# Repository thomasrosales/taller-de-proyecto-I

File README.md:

# Taller de Proyecto I

Ingeniería en Computación - Materia Taller de Proyecto I

## Introducción

Por parte de la cátedra se propuso realizar un vúmetro digital de 8 bandas utilizando la placa de desarrollo EDU-CIAA, un teclado para comunicaicón con el usuario y una matriz de led para la posterior visulización para cumplir con la funcionalidad de un vúmetro.

## Autores

* **Alexandroff, Maximiliano** - *Desarrollo de software y Testeo de PCB* 
* **Gauna, Julián** - *Soldadura de componentes y armado de la PCB*
* **Fernandes Da Ponte, Emir** - *Diseño de PCB* 
* **Rosales, Tomás** - *Desarrollo de software y Testeo de PCB*

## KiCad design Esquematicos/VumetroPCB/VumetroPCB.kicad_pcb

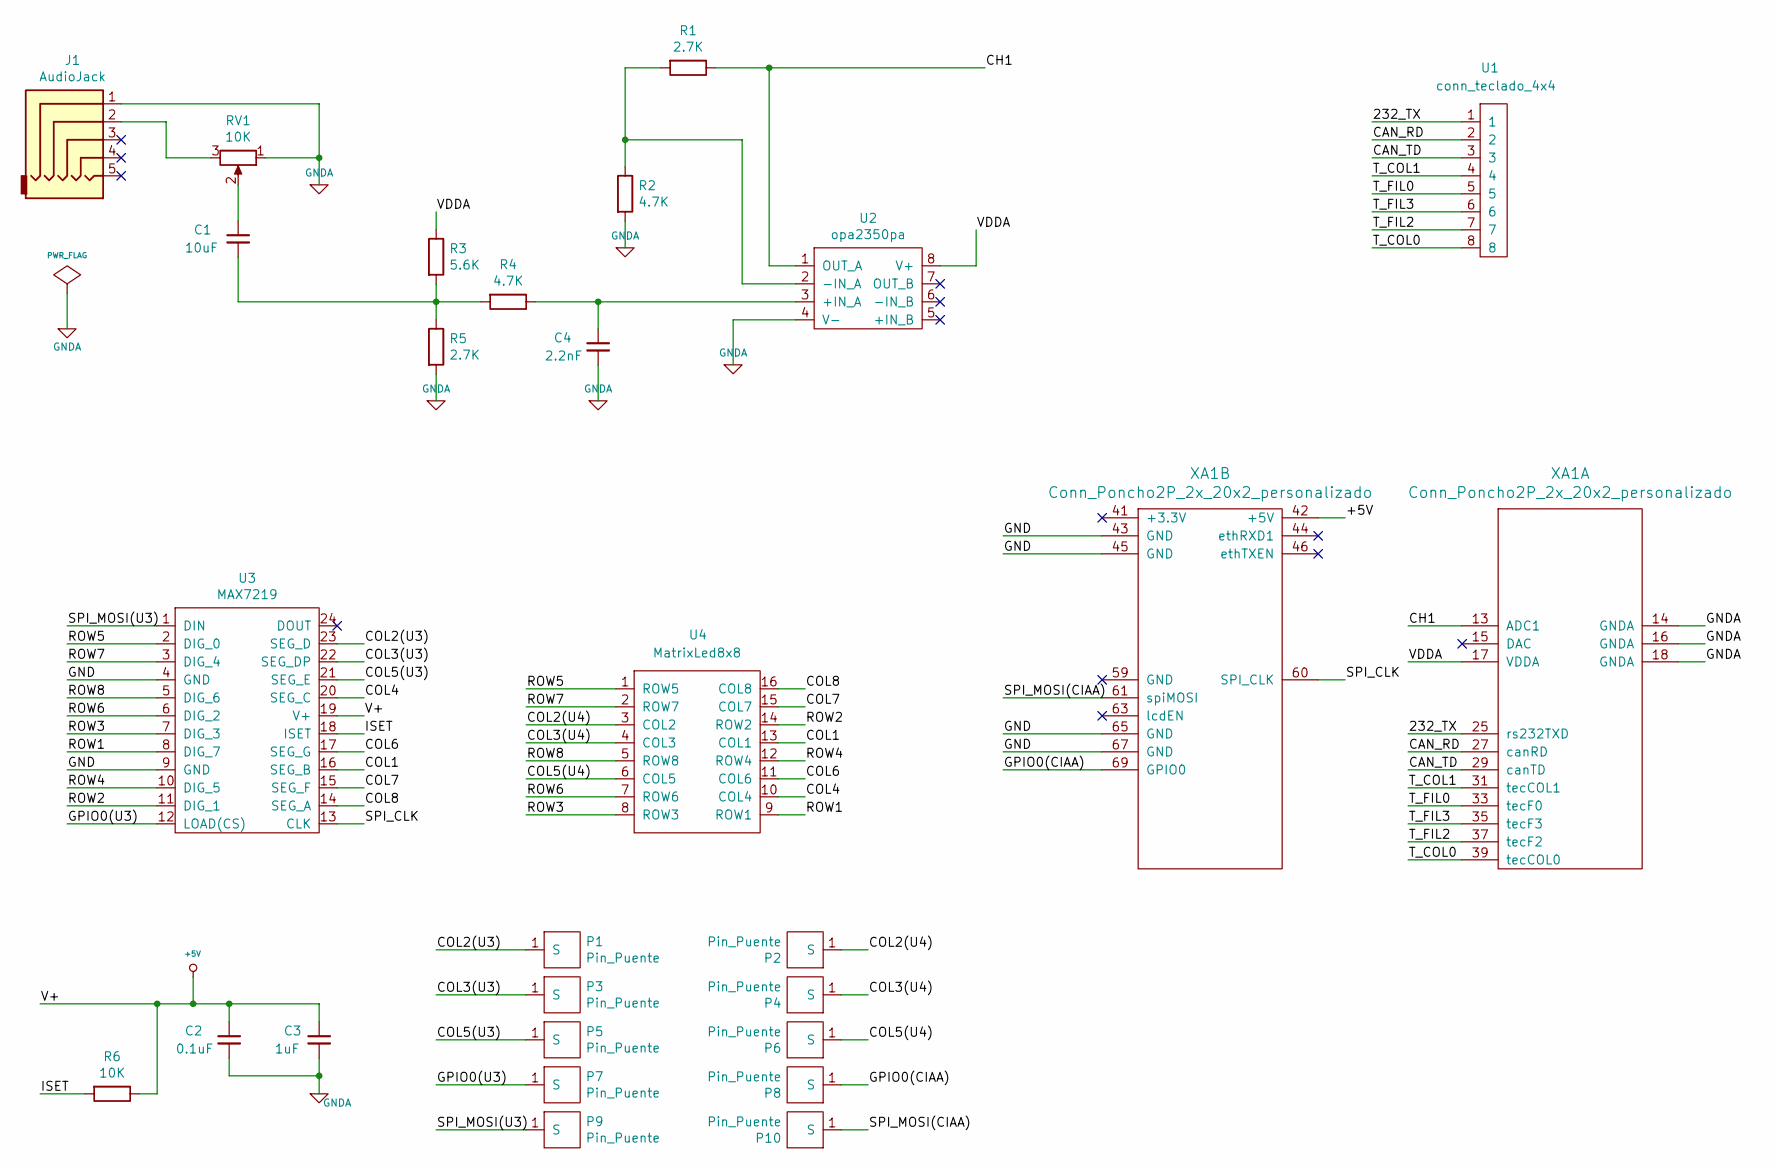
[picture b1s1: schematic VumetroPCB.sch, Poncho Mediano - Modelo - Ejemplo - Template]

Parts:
C1: 10uF; Capacitor
C2: 0.1uF; Capacitor_Disco
C3: 1uF; Capacitor
C4: 2.2nF; Capacitor_Disco
J1: AudioJack
P1, P2, P3, P4, P5, P6, P7, P8, P9, P10: Pin_Puente
R1, R5: 2.7K; Resistor
R2, R4: 4.7K; Resistor
R3: 5.6K; Resistor
R6: 10K; Resistor
RV1: 10K; Potentiometer_Bourns
U1: conn_teclado_4x4; conn_teclado4x4
U2: opa2350pa; OPA2350PA
U3: MAX7219
U4: MatrixLed8x8; Matriz_8x8
XA1: Conn_Poncho2P_2x_20x2_personalizado; Conn_Poncho_Personalizado

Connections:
+5V: C2.1, C3.1, R6.1, U3.19 (V+), XA1.42 (+5V)
/232_TX: U1.1, XA1.25 (rs232TXD)
/CAN_RD: U1.2, XA1.27 (canRD)
/CAN_TD: U1.3, XA1.29 (canTD)
/CH1: R1.1, U2.1 (OUT_A), XA1.13 (ADC1)
/COL1: U3.16 (SEG_B), U4.13 (COL1)
/COL2(U3): P1.1, U3.23 (SEG_D)
/COL2(U4): P2.1, U4.3 (COL2)
/COL3(U3): P3.1, U3.22 (SEG_DP)
/COL3(U4): P4.1, U4.4 (COL3)
/COL4: U3.20 (SEG_C), U4.10 (COL4)
/COL5(U3): P5.1, U3.21 (SEG_E)
/COL5(U4): P6.1, U4.6 (COL5)
/COL6: U3.17 (SEG_G), U4.11 (COL6)
/COL7: U3.15 (SEG_F), U4.15 (COL7)
/COL8: U3.14 (SEG_A), U4.16 (COL8)
/GND: U3.4 (GND), U3.9 (GND), XA1.43 (GND), XA1.45 (GND), XA1.65 (GND), XA1.67 (GND)
/GPIO0(CIAA): P8.1, XA1.69 (GPIO0)
/GPIO0(U3): P7.1, U3.12 (LOAD(CS))
/ISET: R6.2, U3.18 (ISET)
/ROW1: U3.8 (DIG_7), U4.9 (ROW1)
/ROW2: U3.11 (DIG_1), U4.14 (ROW2)
/ROW3: U3.7 (DIG_3), U4.8 (ROW3)
/ROW4: U3.10 (DIG_5), U4.12 (ROW4)
/ROW5: U3.2 (DIG_0), U4.1 (ROW5)
/ROW6: U3.6 (DIG_2), U4.7 (ROW6)
/ROW7: U3.3 (DIG_4), U4.2 (ROW7)
/ROW8: U3.5 (DIG_6), U4.5 (ROW8)
/SPI_CLK: U3.13 (CLK), XA1.60 (SPI_CLK)
/SPI_MOSI(CIAA): P10.1, XA1.61 (spiMOSI)
/SPI_MOSI(U3): P9.1, U3.1 (DIN)
/T_COL0: U1.8, XA1.39 (tecCOL0)
/T_COL1: U1.4, XA1.31 (tecCOL1)
/T_FIL0: U1.5, XA1.33 (tecF0)
/T_FIL2: U1.7, XA1.37 (tecF2)
/T_FIL3: U1.6, XA1.35 (tecF3)
/VDDA: R3.1, U2.8 (V+), XA1.17 (VDDA)
GNDA: C2.2, C3.2, C4.2, J1.1, R2.2, R5.2, RV1.1, U2.4 (V-), XA1.14 (GNDA), XA1.16 (GNDA), XA1.18 (GNDA)
unnamed: C1.1, RV1.2
unnamed: C1.2, R3.2, R4.2, R5.1
unnamed: C4.1, R4.1, U2.3 (+IN_A)
unnamed: J1.2, RV1.3
unnamed: R1.2, R2.1, U2.2 (-IN_A)

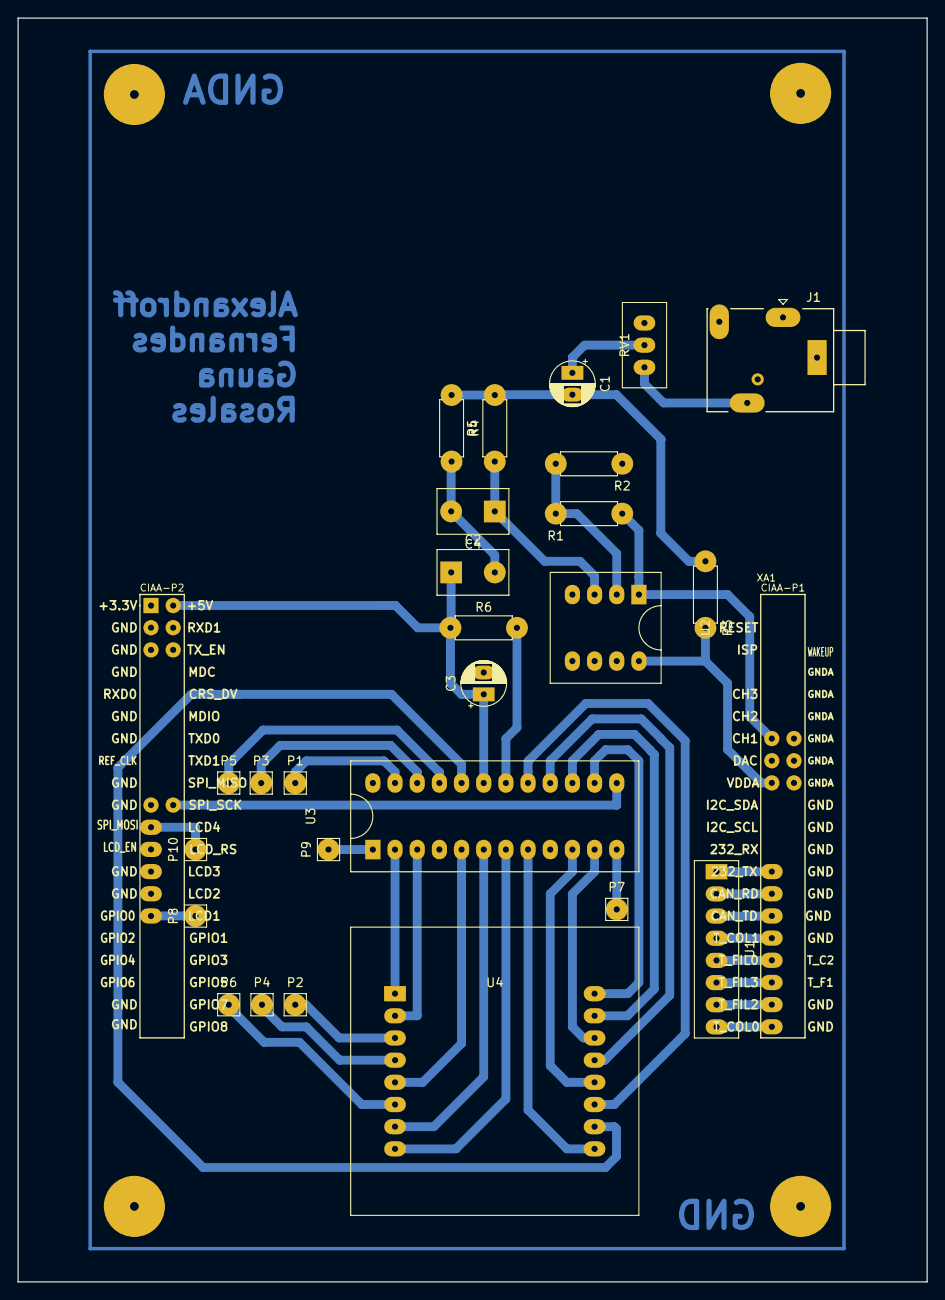
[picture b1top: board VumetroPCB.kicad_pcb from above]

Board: 2 copper layers, 104.1 x 144.8 mm, 27 parts (0 on the bottom side), 43 nets.

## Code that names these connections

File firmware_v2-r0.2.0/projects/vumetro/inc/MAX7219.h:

#ifndef _MAX7219_H_
#define _MAX7219_H_


/*==================[inclusions]=============================================*/
#include "sapi.h"
/*==================[cplusplus]==============================================*/

#ifdef __cplusplus
extern "C" {
#endif

/*==================[macros]=================================================*/
#define ROW1 7
#define ROW2 1
#define ROW3 3
#define ROW4 5
#define ROW5 0
#define ROW6 2
#define ROW7 4
#define ROW8 6

#define COL1 (1 << 5)
#define COL2 (1 << 3)
#define COL3 (1 << 7)
#define COL4 (1 << 4)
#define COL5 (1 << 2)
#define COL6 (1 << 0)
#define COL7 (1 << 1)
#define COL8 (1 << 6)
/*==================[typedef]================================================*/

/*==================[external data declaration]==============================*/

/*==================[external functions declaration]=========================*/
/*
 * Configura el max7219
*/
void MAX7219_init();

/*
 * Configura el modo shutdown
 * 1 -> modo shutdown
 * 0 -> modo normal
*/
void MAX7219_shutdown_mode(bool_t state);
/*
 * Configura el modo displaytest
 * 1 -> modo displaytest
 * 0 -> modo normal
*/
void MAX7219_displaytest_mode(bool_t state);
/*
 * Configura la cantidad de digitos a mostrar
*/
void MAX7219_set_scan_limit(uint8_t cantidad);
/*
 * Escribe la fila pasada como parametro
 * data -> parametro de 8 bits, cada bit representa la columna
 * Ejemplo:
 * Prender columnas 0, 1, 2 de la fila 0
 * MAX7219_write_row(0, 0b00000111)
 * MAX7219_write_row(0, 7)
 * MAXX7219_write_row(0, 0x07)
*/
void MAX7219_write_row(uint8_t row, uint8_t data);
/*
 * Limpia la pantalla de la matriz
*/
void MAX7219_clear_display();
/*
 * Configura la intensidad de la matriz
 * 1 <= intensity <= 16
*/
void MAX7219_set_intensity(uint8_t intensity);

/*==================[cplusplus]==============================================*/

#ifdef __cplusplus
}
#endif

/*==================[end of file]============================================*/
#endif /* #ifndef _MAX7219_H_ */

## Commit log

2018-09-10 el marinero
2018-09-10 el capitan
2018-09-10 Se borra Firmware ciaa
2018-09-10 se agrega firmware estable
2018-09-10 Prueba commit desde eclipse
2018-10-01 correccion de error
2018-10-01 Reestructuracion directorios
2018-10-18 update root
2018-10-18 Documentos nuevos.
2018-10-24 Se crea carpeta esquematicos
2018-10-24 se realiza esquematico en forma parcial
2018-10-25 se agrega amplificador
2018-10-29 Se agrega simulacion de esquematico
2018-10-29 simulacion respuesta en frecuencia
2018-10-30 datasheet
2018-10-30 se agrega elemento a la libreria
2018-10-30 actualización esquemáticoc
2018-10-30 Revert "actualización esquemáticoc"
    This reverts commit c61605e0acc8271fae062afea902648c4f968452.
2018-10-30 se agrega tira de pines a la libreria
2018-10-30 se agrega archivos
2018-10-30 modificacion esquematico
2018-10-30 actualización esquemático matriz de led y driver
2018-10-30 esquematico final
2018-10-30 Se corrige esquematico
2018-11-01 perdon capitan
2018-11-01 correccion esquematico
2018-11-01 documentos
2018-11-08 se agrega firmware_v2 al repo
2018-11-09 Carpeta de adc_fir_dac firmwarev2
2018-11-11 actualización de nombres.
2018-11-12 software
2018-11-13 se agrega proyecto vumetro
2018-11-13 actualización del esquemático se agregar el teclado.
2018-11-14 se corrige libreria de teclado
2018-11-19 se agrega libreria de matriz de led
2018-11-20 Se modifica esquematico
2018-11-20 se agregan mas funciones a la libreria MAX7219
2018-11-20 actualización de filtros
2018-11-20 se comenta la libreria
2018-11-21 filtros funcionando y calculo de potencia
2018-11-21 actualizacion del firmware de filtros
2018-11-21 update filtros
    Se realizó un padding (relleno con ceros) a los filtros para que la convolución circular tanto la señal x[n] como h[n] tengan el mismo tamaño.
2018-11-24 Agregar esquematico del PCB
2018-11-29 Cambiar la huella del potenciometro Bourns3296
2018-12-10 Correcciones al diseño del PCB.
2018-12-12 Arreglar la conexión de la resistencia R3
2018-12-20 se sube avance de proyecto
2018-12-23 Filtros
    Diseño de solución de bandas con filtros FIR creación de bibliotecas:
    FIR, MATH y ampliacióndón del .h del main.
2018-12-26 se realiza proyecto de ejemplo de uso de fft y calculo de potencia
2019-02-14 Arreglo de los errores de diseño en la PCB
2019-02-16 project vumetro
2019-02-23 se lib DSP funcionando
2019-02-24 finalizacion proyecto
2019-02-24 se comenta el codigo
2019-02-24 se corrige DSP.c
